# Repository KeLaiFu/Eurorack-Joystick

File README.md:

# Eurorack-Joystick

Eurorack conversion of the Kosmo format joystick module from Analog Output

https://github.com/holmesrichards/joystick

Current status (12/21/2021):

Main PCB: Layout complete. DRC = 0 errors.
          PCB currently in fabrication, so UNTESTED.
          
Todo: Test with various joystick modules.
      Design PCB panel accordingly.

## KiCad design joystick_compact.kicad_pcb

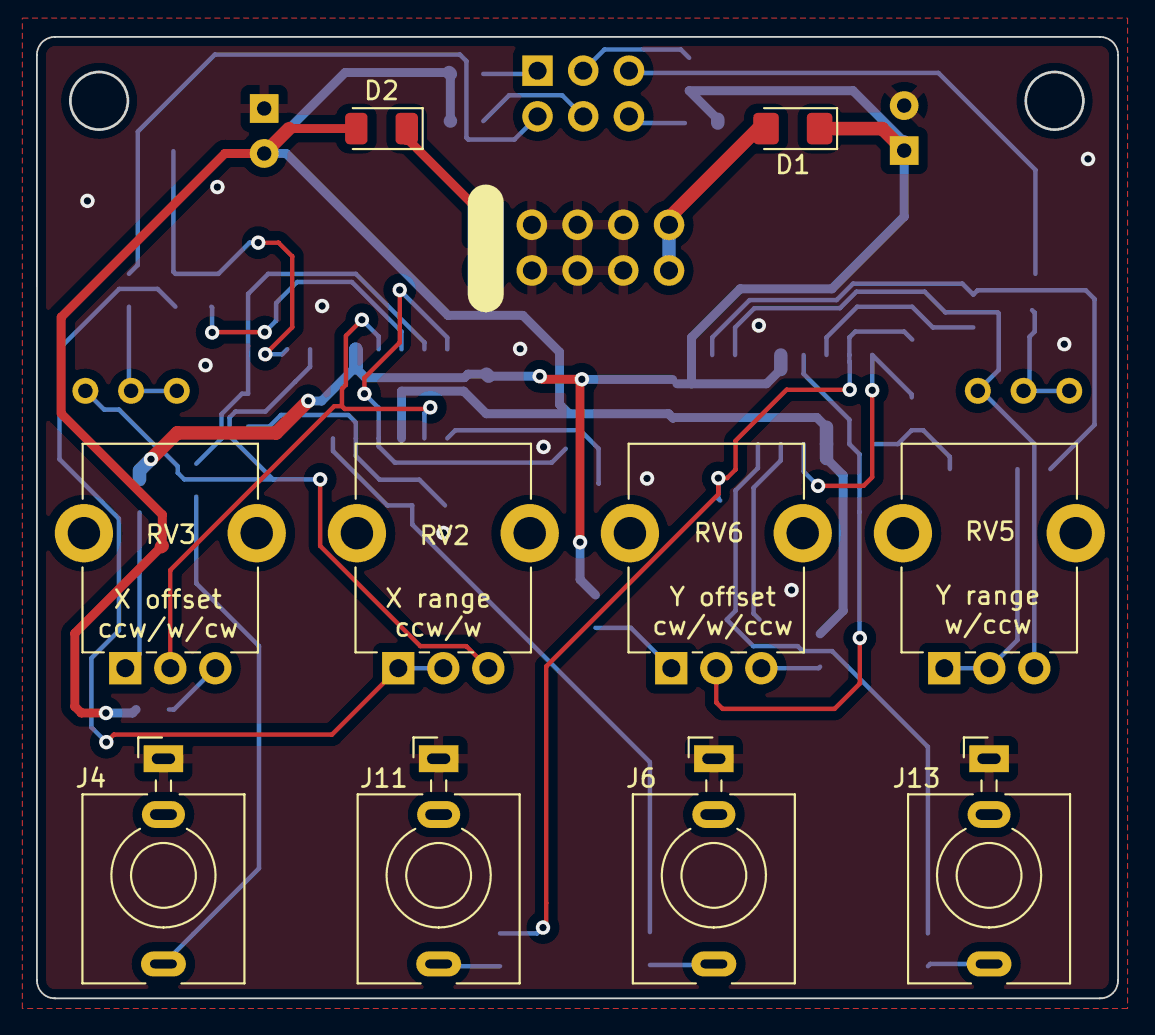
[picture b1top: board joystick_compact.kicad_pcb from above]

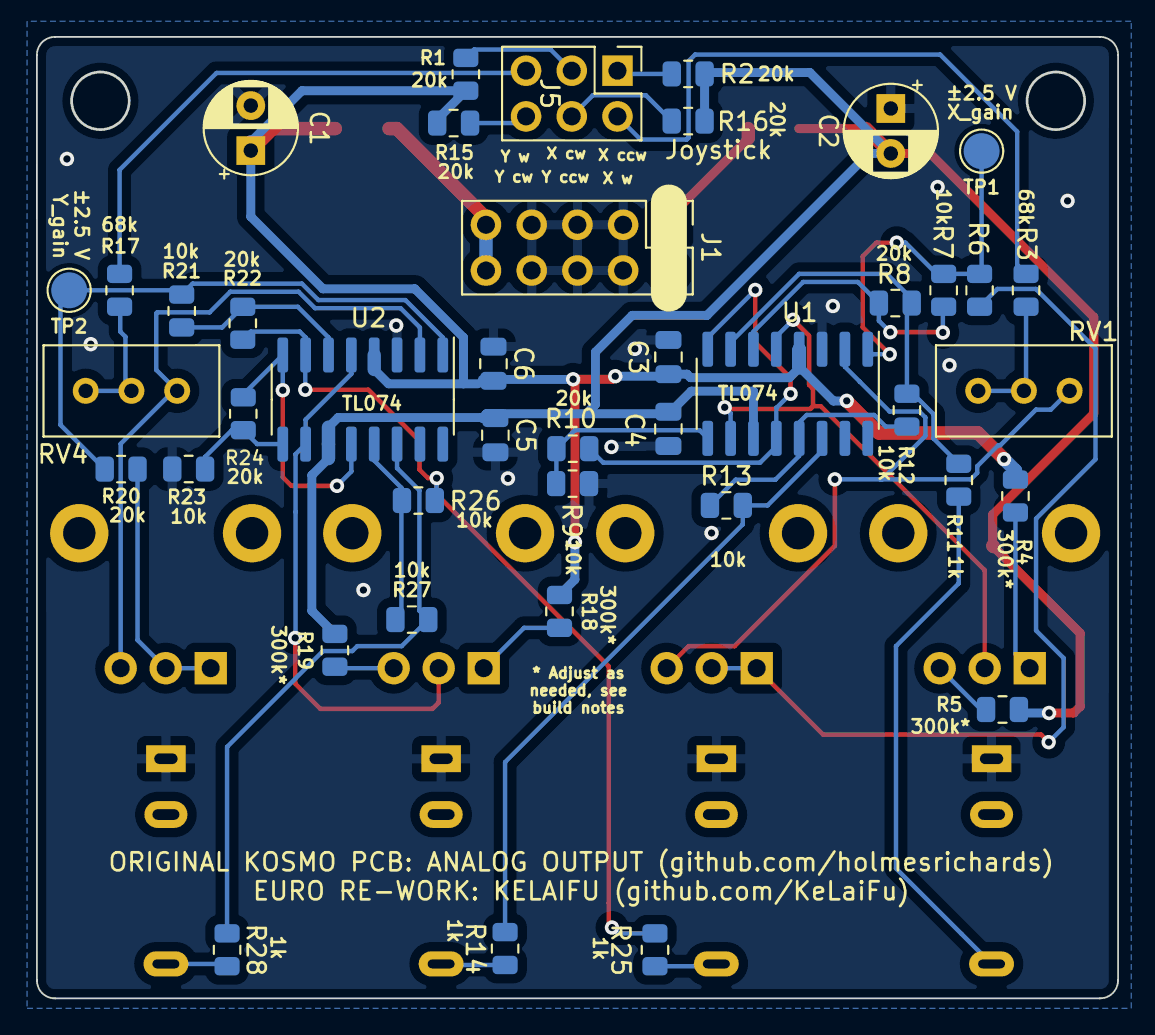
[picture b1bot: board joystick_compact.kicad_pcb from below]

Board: 2 copper layers, 60.0 x 53.4 mm, 52 parts (42 on the bottom side), 41 nets.

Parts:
C1, C2: 10uF; CP_Radial_D5.0mm_P2.50mm
C3, C4, C5, C6: 0.1uF; C_0805_2012Metric
D1: 1N5817; D_1206_3216Metric_Pad1.42x1.75mm_HandSolder
D2: 1N5817; D_1206_3216Metric
J1: Synth_power_2x5; PinHeader_2x05_P2.54mm_Vertical
J4, J6, J11, J13: AudioJack2; 3.5mm_tip_switch_thonkiconn
J5: 6 pin Molex header; PinHeader_2x03_P2.54mm_Vertical
R1, R2, R6, R8, R10, R15, R16, R20, R22, R24: 20k; R_0805_2012Metric
R3, R17: 68k; R_0805_2012Metric
R4, R5, R18, R19: 300k*; R_0805_2012Metric
R7, R9, R12, R13, R21, R23, R26, R27: 10k; R_0805_2012Metric
R11, R14, R25, R28: 1k; R_0805_2012Metric
RV1, RV4: 100k; Potentiometer_Bourns_3296W_Vertical
RV2, RV3, RV5, RV6: B100k; Potentiometer_Alpha_RD901F-40-00D_Single_Vertical_CircularH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
TP1: X_gain; TestPoint_Pad_D2.0mm
TP2: Y_gain; TestPoint_Pad_D2.0mm
U1, U2: TL074; SOIC-16_3.9x9.9mm_P1.27mm

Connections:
+12V: C1.1, C3.1, C6.2, D1.1 (K), R1.1, R4.1, R15.1, R18.1, U1.4 (V+), U2.4 (V+)
-12V: C2.2, C4.2, C5.1, D2.2 (A), R2.2, R5.2, R16.2, R19.2, U1.11 (V-), U2.11 (V-)
/+12_IN: D1.2 (A), J1.9 (+12V), J1.10 (+12V)
/-12_IN: D2.1 (K), J1.1 (-12V), J1.2 (-12V)
/XOUT: J4.T, R11.1
/Y channel/YOUT: J11.T, R25.1
/Y channel/~YOUT: J13.T, R28.1
/~XOUT: J6.T, R14.1
GND: C1.2, C2.1, C3.2, C4.1, C5.2, C6.1, J1.3 (GND), J1.4 (GND), J1.5 (GND), J1.6 (GND), J1.7 (GND), J1.8 (GND), J4.S, J6.S, J11.S, J13.S, R9.2, R23.2, U1.3 (+), U2.3 (+)
unnamed: R3.1, RV1.2, RV1.3
unnamed: R4.2, RV3.1
unnamed: R5.1, RV3.3
unnamed: R6.1, R7.2, TP1.1, U1.1
unnamed: R6.2, RV2.1, RV2.2
unnamed: R7.1, R8.2, U1.6 (-)
unnamed: R10.1, U1.8, U1.12 (+)
unnamed: R9.1, R10.2, U1.9 (-)
unnamed: R8.1, R11.2, R12.2, U1.7
unnamed: R12.1, R13.2, U1.13 (-)
unnamed: R13.1, R14.2, U1.14
unnamed: R17.1, RV4.2, RV4.3
unnamed: R18.2, RV6.1
unnamed: R19.1, RV6.3
unnamed: R20.1, R21.2, TP2.1, U2.1
unnamed: R20.2, RV5.1, RV5.2
unnamed: R21.1, R22.2, U2.6 (-)
unnamed: R22.1, R25.2, R26.2, U2.7
unnamed: R23.1, R24.2, U2.9 (-)
unnamed: R24.1, U2.8, U2.12 (+)
unnamed: R26.1, R27.2, U2.13 (-)
unnamed: R27.1, R28.2, U2.14
unnamed: RV1.1, RV2.3, U1.2 (-)
unnamed: RV3.2, U1.5 (+), U1.10 (+)
unnamed: RV4.1, RV5.3, U2.2 (-)
unnamed: RV6.2, U2.5 (+), U2.10 (+)
XPOT_CCW: J5.1, R2.1
XPOT_CW: J5.3, R1.2
XPOT_WIPER: J5.2, R3.2
YPOT_CCW: J5.4, R16.1
YPOT_CW: J5.6, R15.2
YPOT_WIPER: J5.5, R17.2
